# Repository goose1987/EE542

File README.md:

EE542
=====
report variable

temperature
voltage
current
efficiency
location?

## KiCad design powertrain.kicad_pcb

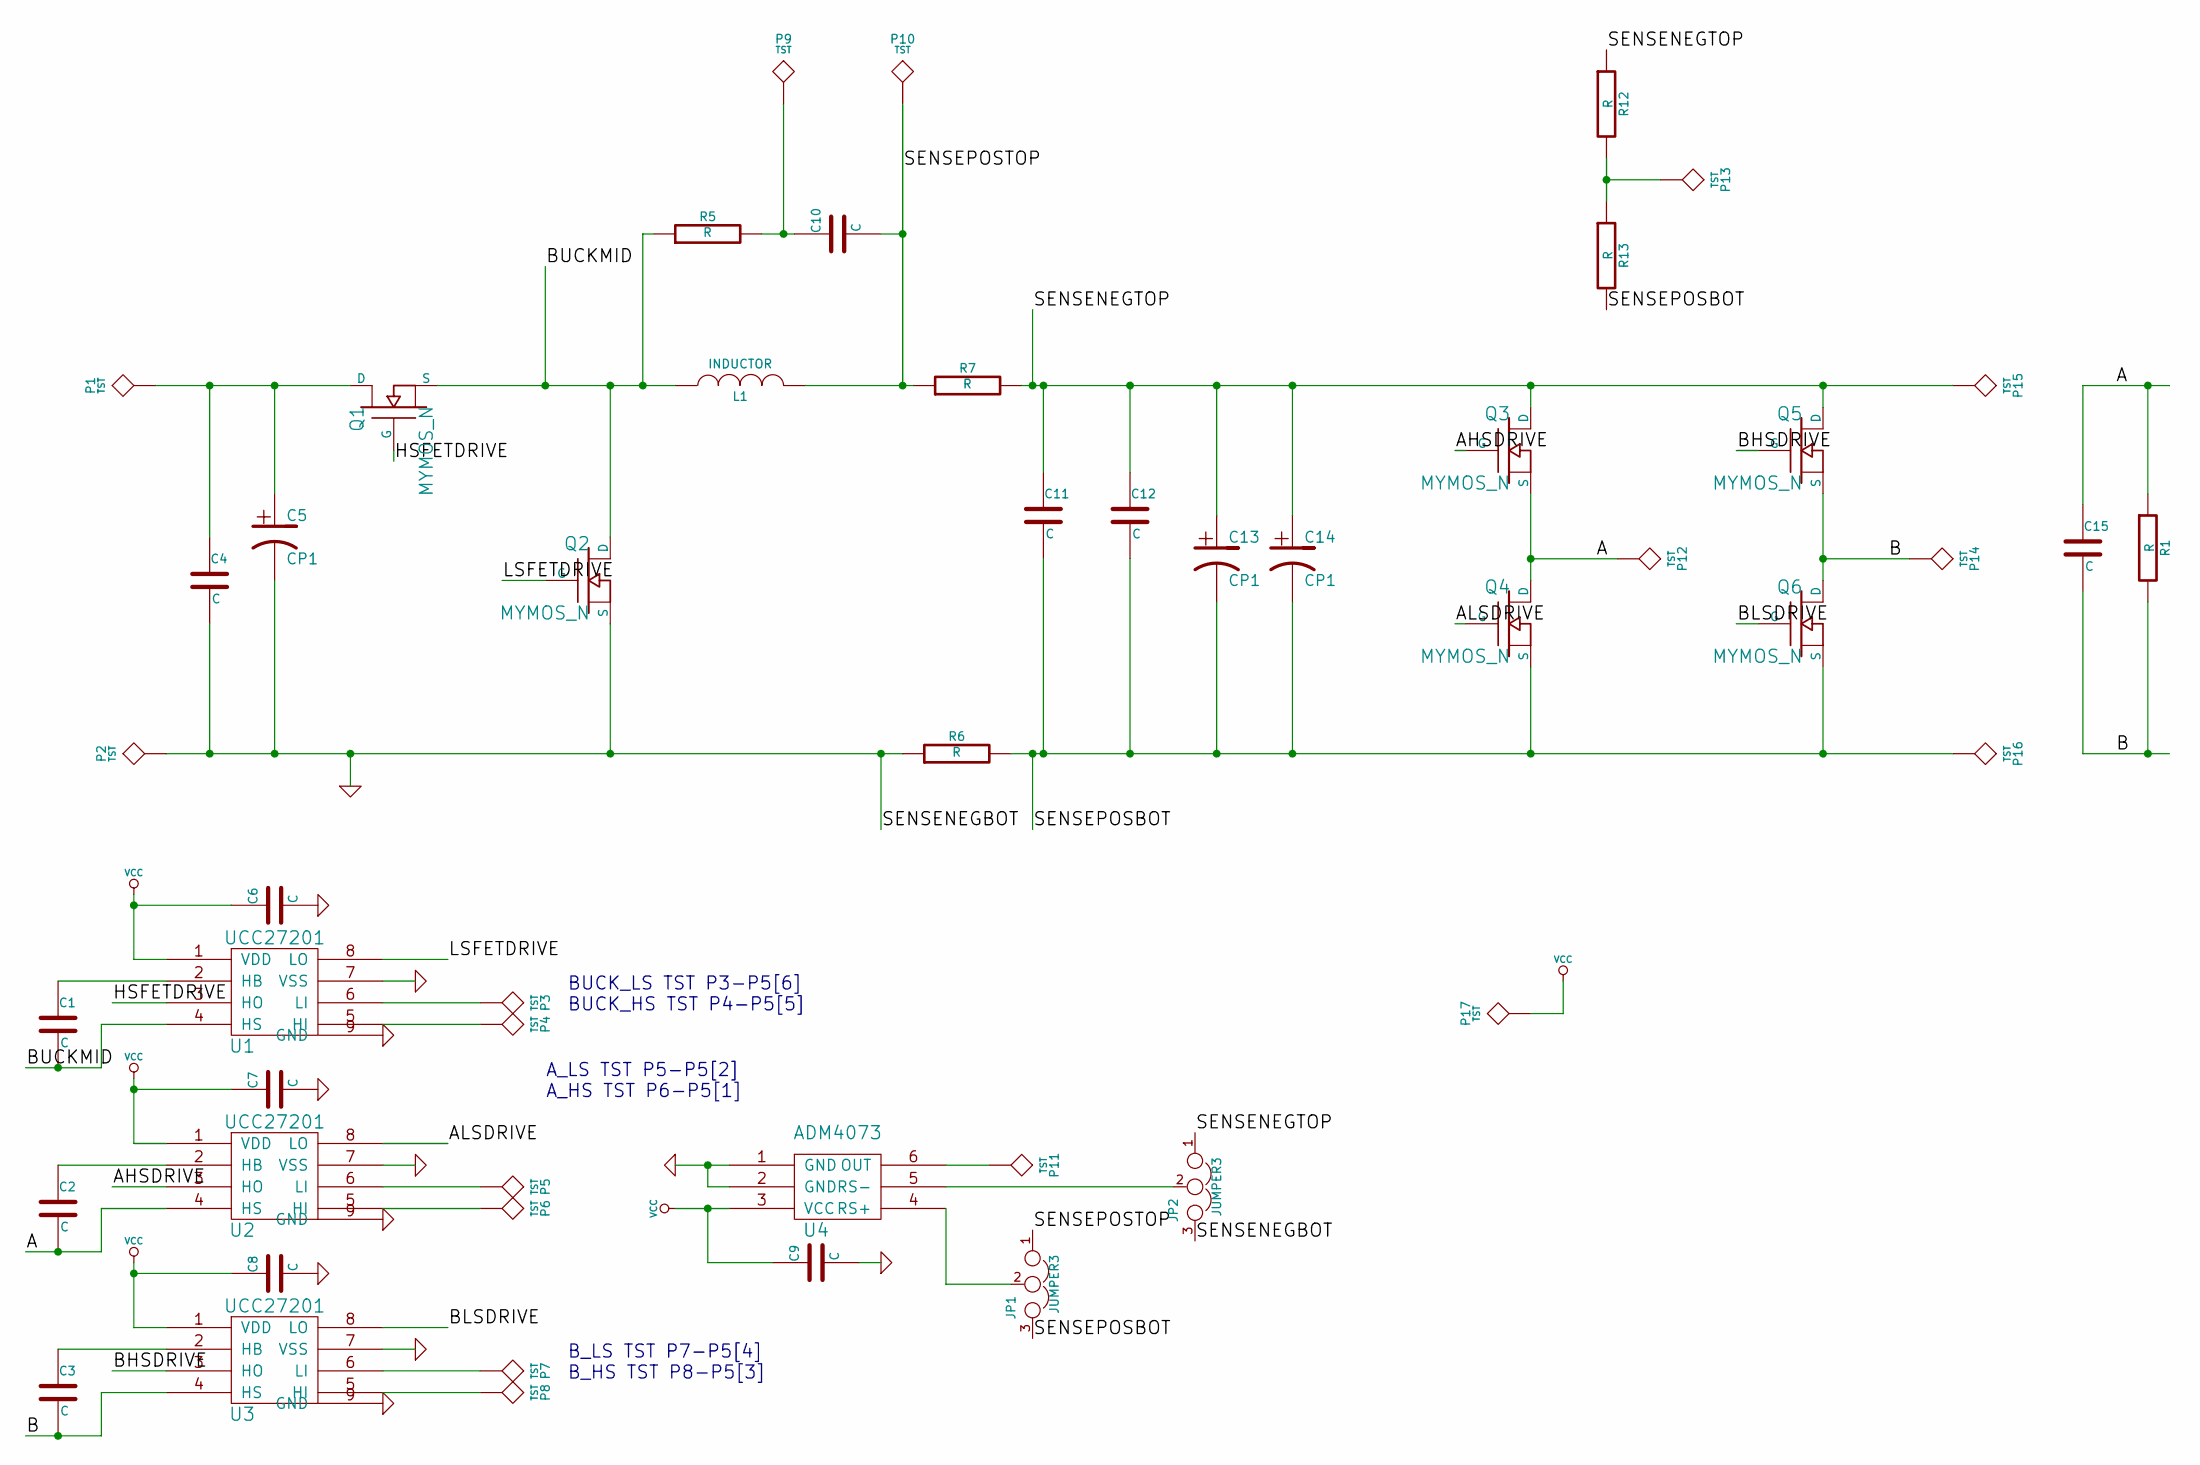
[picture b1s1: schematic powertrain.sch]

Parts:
C1, C2, C3, C4, C6, C7, C8, C9, C10, C11, C12, C15: C
C5, C13, C14: CP1
JP1, JP2: JUMPER3
L1: INDUCTOR
P1, P2, P3, P4, P5, P6, P7, P8, P9, P10, P11, P12, P13, P14, P15, P16, P17: TST
Q1, Q2, Q3, Q4, Q5, Q6: MYMOS_N
R1, R5, R6, R7, R12, R13: R
U1, U2, U3: UCC27201
U4: ADM4073

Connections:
/A: C2.2, C15.1, P12.1, Q3.3 (S), Q4.2 (D), R1.1, U2.4 (HS)
/AHSDRIVE: Q3.1 (G), U2.3 (HO)
/ALSDRIVE: Q4.1 (G), U2.8 (LO)
/B: C3.2, C15.2, P14.1, Q5.3 (S), Q6.2 (D), R1.2, U3.4 (HS)
/BHSDRIVE: Q5.1 (G), U3.3 (HO)
/BLSDRIVE: Q6.1 (G), U3.8 (LO)
/BUCKMID: C1.2, L1.1, Q1.3 (S), Q2.2 (D), R5.1, U1.4 (HS)
/HSFETDRIVE: Q1.1 (G), U1.3 (HO)
/LSFETDRIVE: Q2.1 (G), U1.8 (LO)
/SENSENEGTOP: C11.1, C12.1, C13.1, C14.1, JP2.1, P15.1, Q3.2 (D), Q5.2 (D), R7.2, R12.1
/SENSEPOSBOT: C11.2, C12.2, C13.2, C14.2, JP1.3, P16.1, Q4.3 (S), Q6.3 (S), R6.2, R13.2
/SENSEPOSTOP: C10.2, JP1.1, L1.2, P10.1, R7.1
GND: C4.2, C5.2, C6.2, C7.2, C8.2, C9.2, JP2.3, P2.1, Q2.3 (S), R6.1, U1.7 (VSS), U1.9 (GND), U2.7 (VSS), U2.9 (GND), U3.7 (VSS), U3.9 (GND), U4.1 (GND), U4.2 (GND)
unnamed: C1.1, U1.2 (HB)
unnamed: C3.1, U3.2 (HB)
unnamed: C2.1, U2.2 (HB)
unnamed: C10.1, P9.1, R5.2
unnamed: P11.1, U4.6 (OUT)
unnamed: P13.1, R12.2, R13.1
unnamed: JP2.2, U4.5 (RS-)
unnamed: JP1.2, U4.4 (RS+)
unnamed: P8.1, U3.5 (HI)
unnamed: C4.1, C5.1, P1.1, Q1.2 (D)
unnamed: P4.1, U1.5 (HI)
unnamed: P3.1, U1.6 (LI)
unnamed: P7.1, U3.6 (LI)
unnamed: P6.1, U2.5 (HI)
unnamed: P5.1, U2.6 (LI)
VCC: C6.1, C7.1, C8.1, C9.1, P17.1, U1.1 (VDD), U2.1 (VDD), U3.1 (VDD), U4.3 (VCC)

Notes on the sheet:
BUCK_LS TST P3-P5[6] BUCK_HS TST P4-P5[5]
A_LS TST P5-P5[2] A_HS TST P6-P5[1]
B_LS TST P7-P5[4] B_HS TST P8-P5[3]

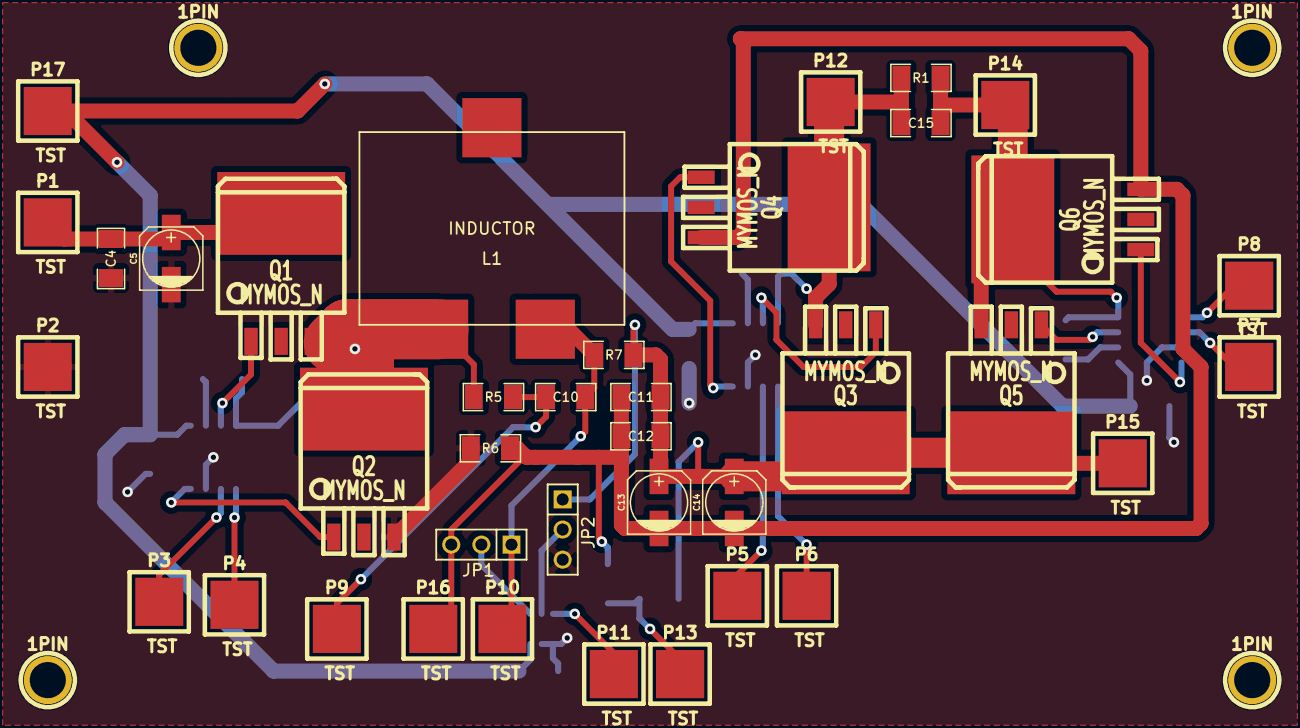
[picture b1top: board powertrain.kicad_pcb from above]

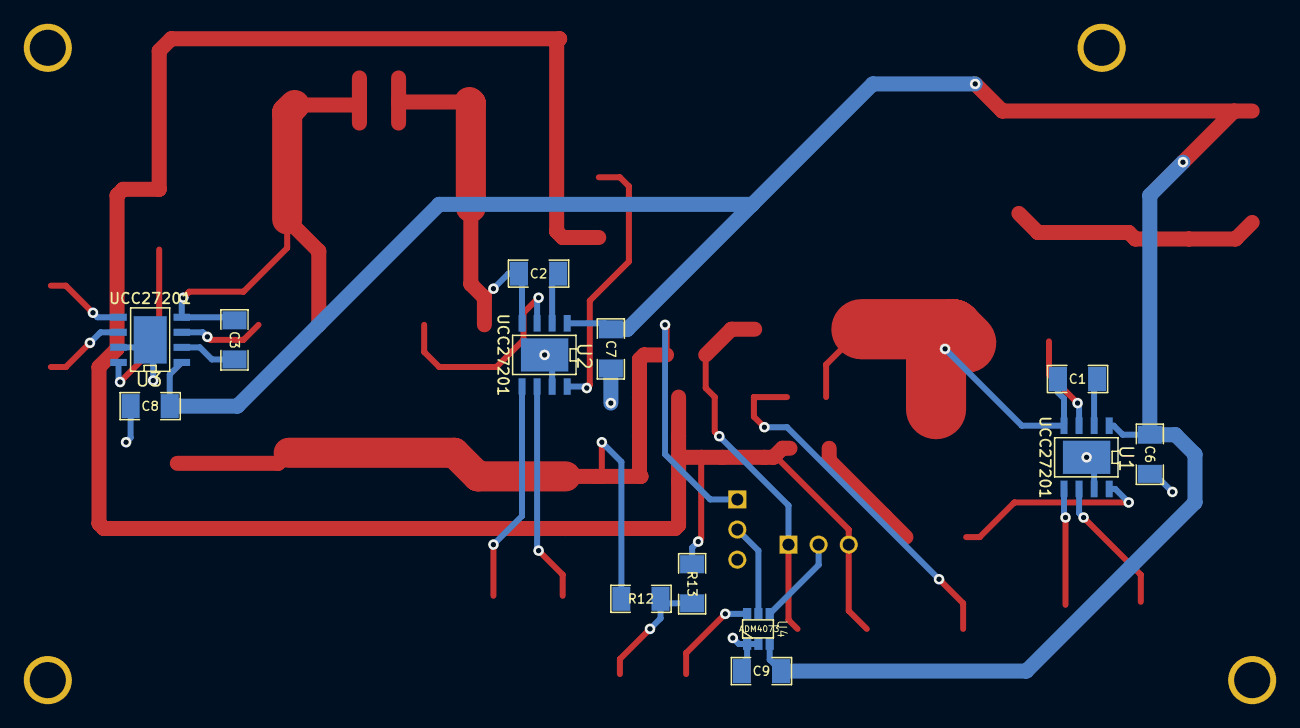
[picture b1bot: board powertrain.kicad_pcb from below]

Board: 2 copper layers, 55 parts (13 on the bottom side), 29 nets.

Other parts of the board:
1PIN, 1PIN#2, 1PIN#3, 1PIN#4: P***; 1pin

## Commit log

2014-10-07 initial commit
    layout for power train
2014-10-07 housecleaning
    deleted gerber zip
2014-10-08 added abstract for Peckol
    abstract of project goal and strategy
2014-10-26 Added PSoC and dev board documents
2014-10-26 Added PSoC documents
2014-10-27 created psoc 5 project with basic components PWM ADC Clock
2014-10-27 added message
2014-10-29 Changes to invert
2014-10-29 Added digital control docs
2014-10-29 added talk 1 power point
2014-10-29 micro inverter document
2014-10-31 changed SAR ADC name to ADC_SAR_V added csv bom file for power train
2014-10-31 got pwm to work delta sigma ADC to sense the voltage divider and modulate PWM
2014-11-03 presentation updates
2014-11-03 more presentation updates
2014-11-04 added sine LUT need to change to a rectified sine LUT for duty cycle control
2014-11-06 added UART
2014-11-06 added android app folder added solarbug application
2014-11-06 invert updates
2014-11-06 deleted old solarbug app added new solarbug app
2014-11-06 solarbug sync
2014-11-07 copied over an android project from another folder
2014-11-07 edited message
2014-11-07 added atcommand for arduino bluetooth config
2014-11-09 UART working
2014-11-09 editted README file with report variables
2014-11-09 added ltspice sim
2014-11-09 added SPI block renamed port pins for consistency and clarity
2014-11-11 added webserver folder for server side code for storing and graphing data from sparkcore
2014-11-14 touched invert psoc creator project file created m script for control design
2014-11-14 added example chart html added m script for real this time, did not add in previous commit
2014-11-14 added control
2014-11-15 open loop PWM with half sine works
2014-11-15 open loop inverter work scope capture on USB added new pcb footprint lib modified board layout
2014-11-16 messed around with the webserver added plotly
2014-11-17 Added K factor
2014-11-18 updated javascript and HTML
2014-11-18 added periodic function to check for voltage measurement from the sparkcore
2014-11-21 added stream.js streaming plot from spark
2014-11-21 changed vsense pin back to voltage divider to test webserver
2014-11-21 added documentation folder with scope capture
2014-11-21 added tracking for sparkcore code binary file (compiled version) arduino style .ino file
2014-11-24 fixed html bug in iframe, missing closing tag
2014-11-24 added code to tie into the tinker app on iphone added empty function for querying temperature and amperage cleaned psoc project
2014-11-27 added separate isr to update duty cycle of PWM every cycle added separate counter and isr ~15100 Hz to update LUT pointer enlarged schematic sheet renamed a bunch of crap
2014-11-27 enable and start LOOP and LUT isr
2014-12-05 buck working with 60Hz sine
2014-12-05 working PI
2014-12-06 tweaked unfolder algorithm
2014-12-08 got DFB working to calculate RMS integrated with PI PI still works as of this commit
2014-12-08 raised the clock speed via PLL to 48 MHz currently reading potentiometer to calculate rms p6[5] ADC running at 30kHz start and stop DFB as needed
2014-12-09 added SAR ADC for capturing current DFB is used to calculated RMS current send rms current through UART when requested by spark
2014-12-09 removed old server file added new server app
